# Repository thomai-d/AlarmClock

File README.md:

# AlarmClock
Arduino based alarm clock with wake up light

## Features
* Two individually configurable alarm times
* 15 minutes before alarm, the power-LED is slowly ramped on
* LED wake up color is configurable by the user
* Slowly rising acoustic alarm
* Temperature and air pressure trend for the last 8 hours
* Display brightness is automatically reduced in the dark (LDR)
* Power fail safe (battery buffered RTC)

## Hardware
* atmega328 @ 16MHz
* 2.8" SPI TFT Screen (320x240) with ILI9331 controller
* DS3231 battery buffered RTC with I2C interface
* BMP180 temperature / pressure sensor with I2C interface
* High Power RGB-LED (~4.5W)
* Eagle files / part list included

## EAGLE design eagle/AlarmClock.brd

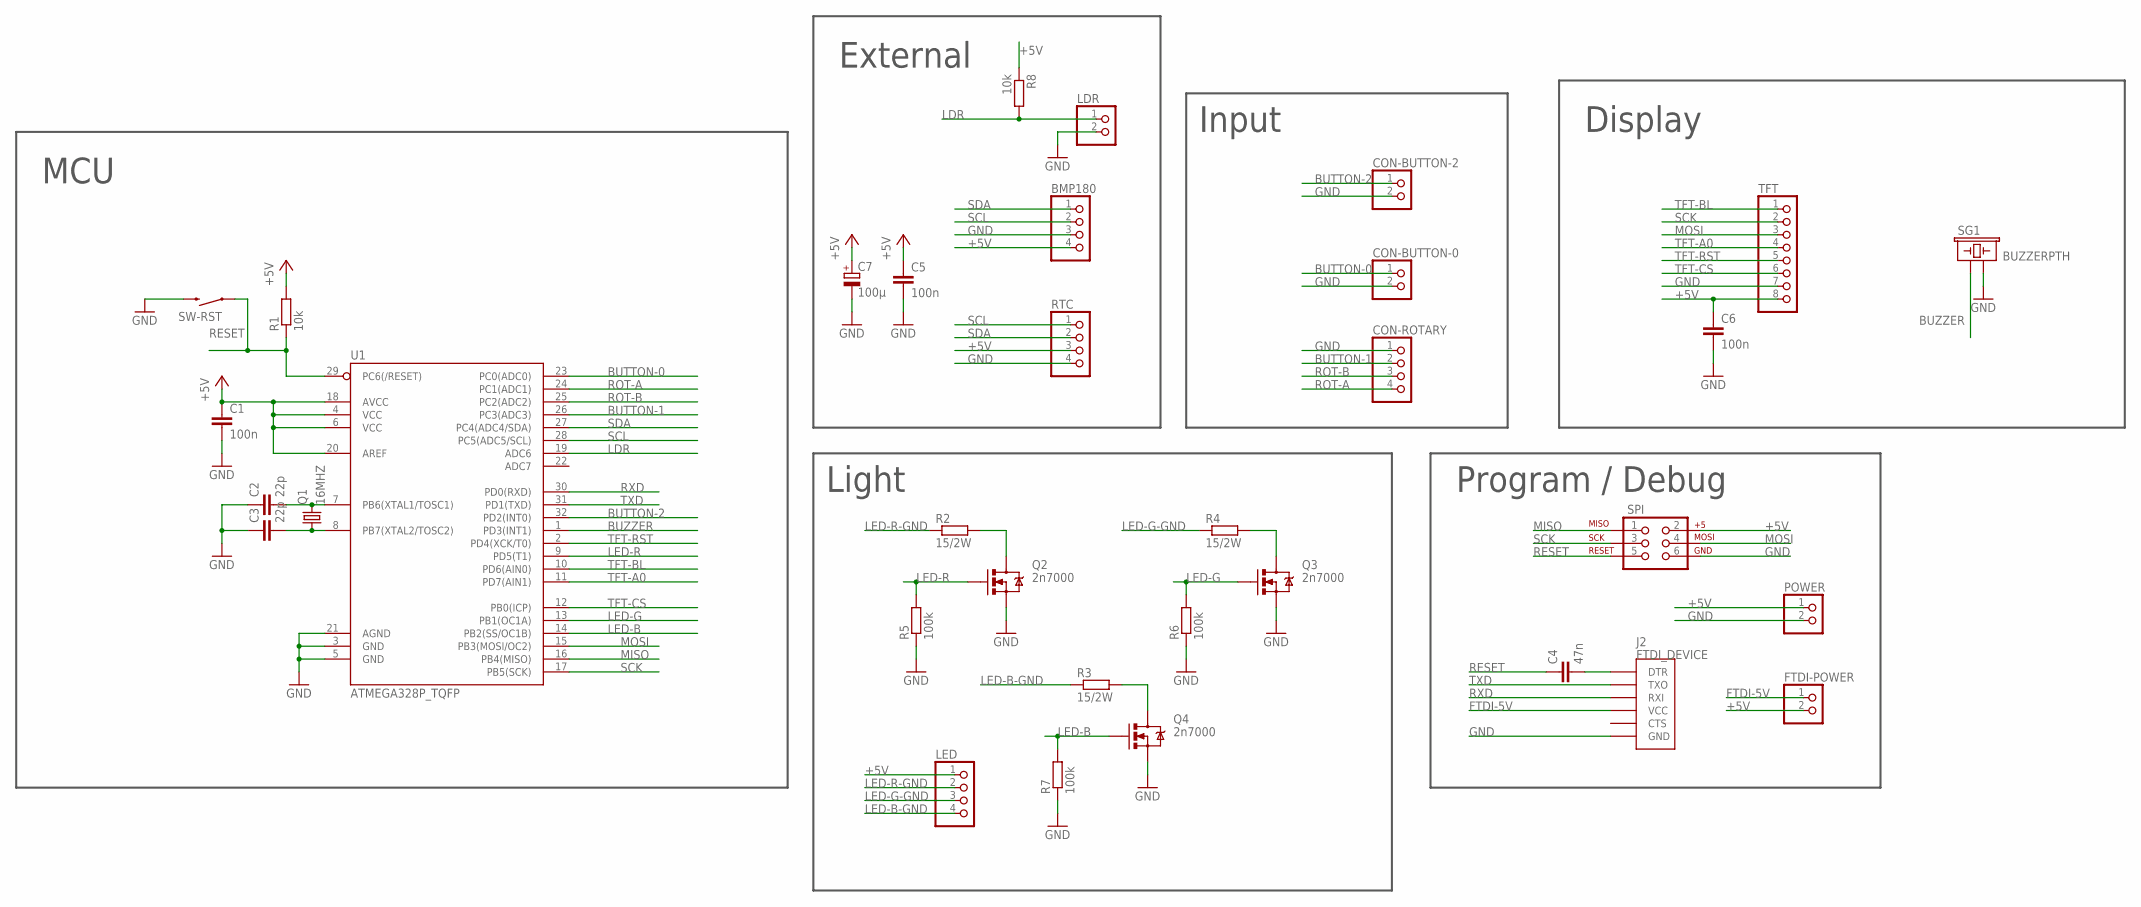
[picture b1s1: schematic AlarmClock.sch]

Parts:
BMP180: 1X04
C1, C5, C6: 100n; C0805
C2, C3: 22p; C0805
C4: 47n; C0805
C7: 100µ; PANASONIC_F
CON-BUTTON-0, CON-BUTTON-2: 1X02/90
CON-ROTARY: 1X04/90
FTDI-POWER: 1X02
J2: FTDI_DEVICE; FTDI_DEVICE_SIDE
LDR: 1X02
LED: 1X04
POWER: 1X02
Q1: 16MHZ; HC49UP
Q2, Q3, Q4: 2n7000; TO-92
R1: 10k; M0805
R2, R3, R4: 15/2W; 0414/15
R5, R6, R7: 100k; M0805
R8: 10k; R0805
RTC: 1X04
SG1: BUZZERPTH; BUZZER-12MM
SPI: AVR_SPI_PRG_6NS; 2X3-NS
SW-RST: SWITCH-MOMENTARY-2SMD-1101NE; TACTILE-SWITCH-1101NE
TFT: 1X08
U1: ATMEGA328P_TQFP; TQFP32-08

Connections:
+5V: BMP180.4, C1.1, C5.1, C6.1, C7.+, FTDI-POWER.2, LED.1, POWER.1, R1.2, R8.1, RTC.3, SPI.2, TFT.8, U1.4 (VCC), U1.6 (VCC), U1.18 (AVCC), U1.20 (AREF)
BUTTON-0: CON-BUTTON-0.1, U1.23 (PC0(ADC0))
BUTTON-1: CON-ROTARY.2, U1.26 (PC3(ADC3))
BUTTON-2: CON-BUTTON-2.1, U1.32 (PD2(INT0))
BUZZER: SG1.+ (1), U1.1 (PD3(INT1))
FTDI-5V: FTDI-POWER.1, J2.P$4 (VCC)
GND: BMP180.3, C1.2, C2.1, C3.1, C5.2, C6.2, C7.-, CON-BUTTON-0.2, CON-BUTTON-2.2, CON-ROTARY.1, J2.P$6 (GND), LDR.2, POWER.2, Q2.1 (S), Q3.1 (S), Q4.1 (S), R5.1, R6.1, R7.1, RTC.4, SG1.- (2), SPI.6, SW-RST.2, TFT.7, U1.3 (GND), U1.5 (GND), U1.21 (AGND)
LDR: LDR.1, R8.2, U1.19 (ADC6)
LED-B: Q4.2 (G), R7.2, U1.14 (PB2(SS/OC1B))
LED-B-GND: LED.4, R3.1
LED-G: Q3.2 (G), R6.2, U1.13 (PB1(OC1A))
LED-G-GND: LED.3, R4.1
LED-R: Q2.2 (G), R5.2, U1.9 (PD5(T1))
LED-R-GND: LED.2, R2.1
MISO: SPI.1, U1.16 (PB4(MISO))
MOSI: SPI.4, TFT.3, U1.15 (PB3(MOSI/OC2))
unnamed: C4.2, J2.P$1 (DTR)
unnamed: C2.2, Q1.2, U1.7 (PB6(XTAL1/TOSC1))
unnamed: C3.2, Q1.1, U1.8 (PB7(XTAL2/TOSC2))
unnamed: Q2.3 (D), R2.2
unnamed: Q3.3 (D), R4.2
unnamed: Q4.3 (D), R3.2
RESET: C4.1, R1.1, SPI.5, SW-RST.1, U1.29 (PC6(/RESET))
ROT-A: CON-ROTARY.4, U1.24 (PC1(ADC1))
ROT-B: CON-ROTARY.3, U1.25 (PC2(ADC2))
RXD: J2.P$3 (RXI), U1.30 (PD0(RXD))
SCK: SPI.3, TFT.2, U1.17 (PB5(SCK))
SCL: BMP180.2, RTC.1, U1.28 (PC5(ADC5/SCL))
SDA: BMP180.1, RTC.2, U1.27 (PC4(ADC4/SDA))
TFT-A0: TFT.4, U1.11 (PD7(AIN1))
TFT-BL: TFT.1, U1.10 (PD6(AIN0))
TFT-CS: TFT.6, U1.12 (PB0(ICP))
TFT-RST: TFT.5, U1.2 (PD4(XCK/T0))
TXD: J2.P$2 (TXO), U1.31 (PD1(TXD))

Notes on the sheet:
External
Input
Light
Program / Debug
Display
MCU

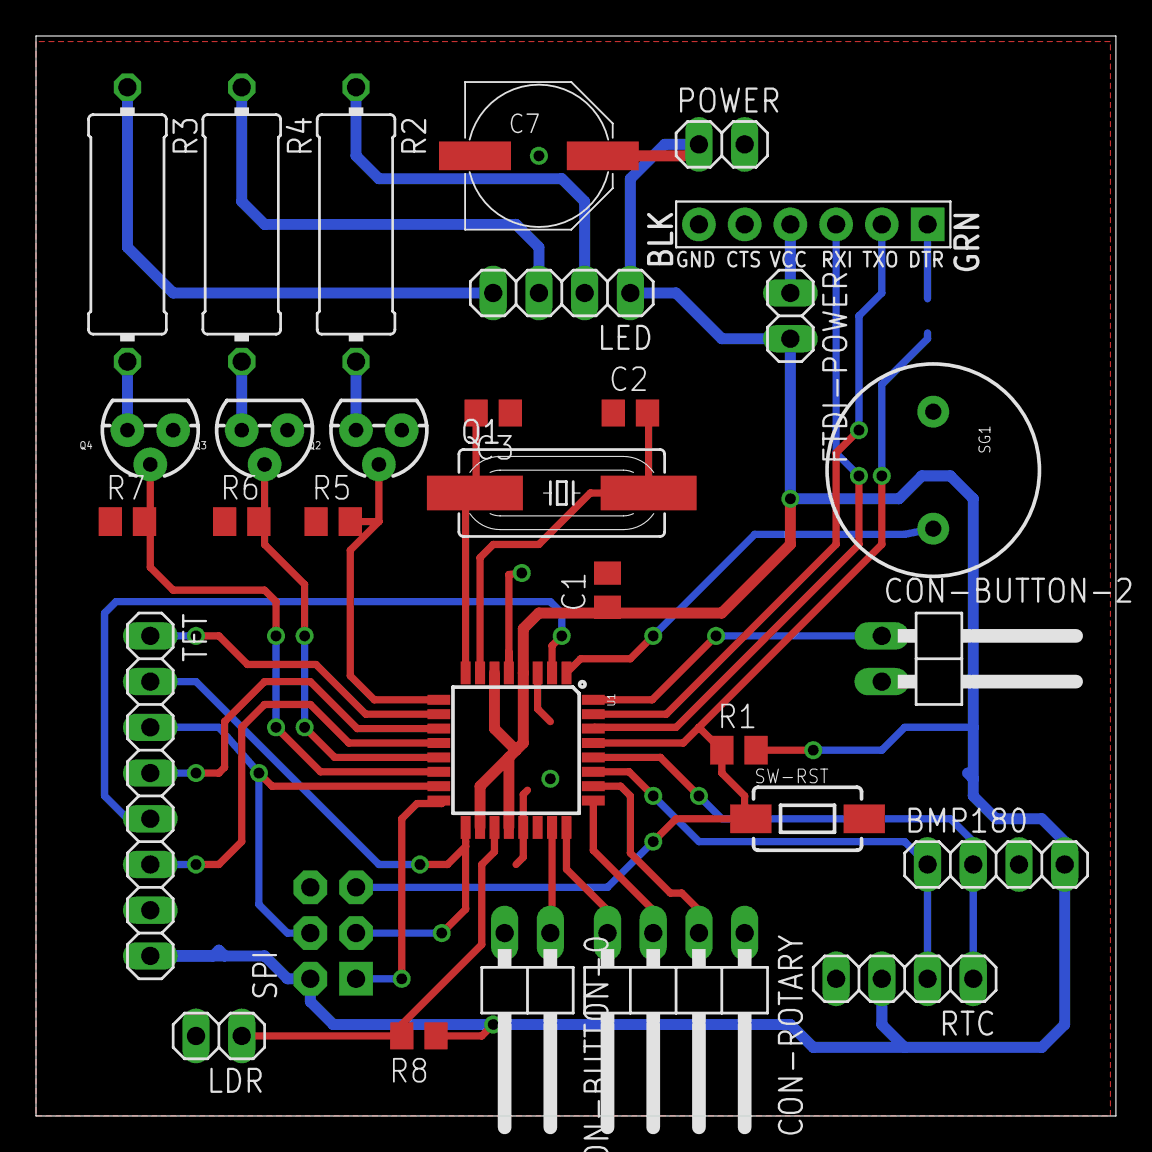
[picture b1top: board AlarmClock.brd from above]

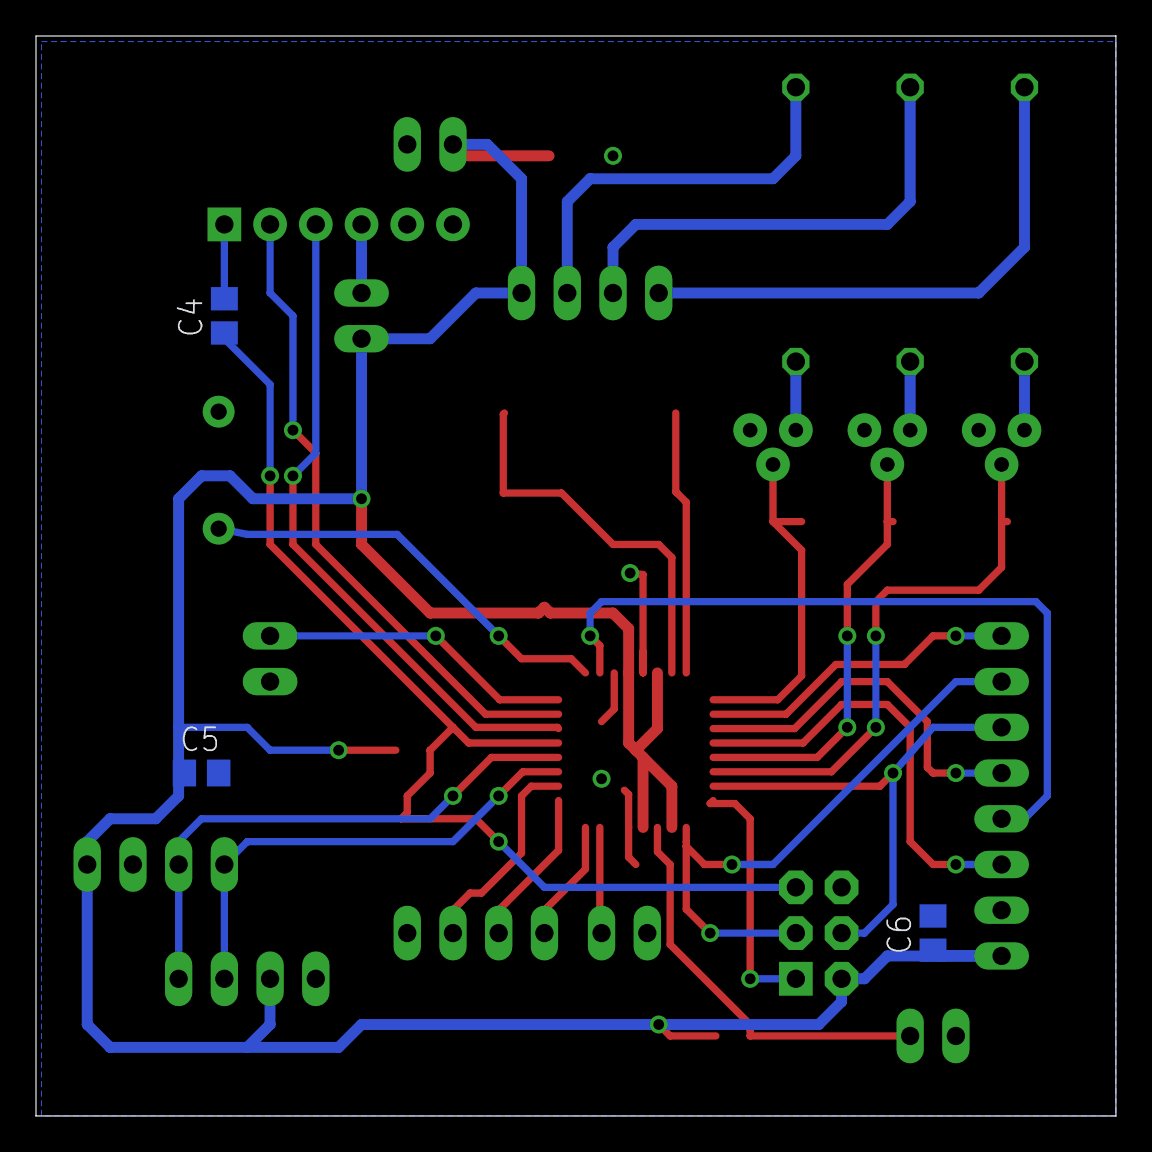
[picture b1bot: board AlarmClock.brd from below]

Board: 2 copper layers, 60.0 x 60.0 mm, 34 parts (3 on the bottom side), 34 nets.

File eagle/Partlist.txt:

Partlist

Exported from AlarmClock.sch at 08.12.2016 19:17

EAGLE Version 7.6.0 Copyright (c) 1988-2016 CadSoft

Assembly variant: 

Part         Value           Device                       Package               Library                    Sheet

BMP180                       PINHD-1X4                    1X04                  pinhead                    1
C1           100n            C-EUC0805                    C0805                 resistor                   1
C2           22p             C-EUC0805                    C0805                 resistor                   1
C3           22p             C-EUC0805                    C0805                 resistor                   1
C4           47n             C-EUC0805                    C0805                 resistor                   1
C5           100n            C-EUC0805                    C0805                 resistor                   1
C6           100n            C-EUC0805                    C0805                 resistor                   1
C7           100µ            CPOL-EUF                     PANASONIC_F           resistor                   1
CON-BUTTON-0                 PINHD-1X2/90                 1X02/90               pinhead                    1
CON-BUTTON-2                 PINHD-1X2/90                 1X02/90               pinhead                    1
CON-ROTARY                   PINHD-1X4/90                 1X04/90               pinhead                    1
FTDI-POWER                   PINHD-1X2                    1X02                  pinhead                    1
J2           FTDI_DEVICE     FTDI_DEVICE                  FTDI_DEVICE_SIDE      SparkFun-Connectors        1
LDR                          PINHD-1X2                    1X02                  pinhead                    1
LED                          PINHD-1X4                    1X04                  pinhead                    1
POWER                        PINHD-1X2                    1X02                  pinhead                    1
Q1           16MHZ           CRYSTALHC49UP                HC49UP                crystal                    1
Q2           2n7000          MOSFET-NCHANNEL2N7000        TO-92                 SparkFun-DiscreteSemi      1
Q3           2n7000          MOSFET-NCHANNEL2N7000        TO-92                 SparkFun-DiscreteSemi      1
Q4           2n7000          MOSFET-NCHANNEL2N7000        TO-92                 SparkFun-DiscreteSemi      1
R1           10k             R-EU_M0805                   M0805                 resistor                   1
R2           15/2W           R-EU_0414/15                 0414/15               resistor                   1
R3           15/2W           R-EU_0414/15                 0414/15               resistor                   1
R4           15/2W           R-EU_0414/15                 0414/15               resistor                   1
R5           100k            R-EU_M0805                   M0805                 resistor                   1
R6           100k            R-EU_M0805                   M0805                 resistor                   1
R7           100k            R-EU_M0805                   M0805                 resistor                   1
R8           10k             R-EU_R0805                   R0805                 resistor                   1
RTC                          PINHD-1X4                    1X04                  pinhead                    1
SG1          BUZZERPTH       BUZZERPTH                    BUZZER-12MM           SparkFun-Electromechanical 1
SPI                          AVR_SPI_PRG_6NS              2X3-NS                SparkFun-Connectors        1
SW-RST                       SWITCH-MOMENTARY-2SMD-1101NE TACTILE-SWITCH-1101NE SparkFun-Electromechanical 1
TFT                          PINHD-1X8                    1X08                  pinhead                    1
U1           ATMEGA328P_TQFP ATMEGA328P_TQFP              TQFP32-08             SparkFun-DigitalIC         1

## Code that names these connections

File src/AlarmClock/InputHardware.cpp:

#include "InputHardware.h"

const uint8_t InputHardwareClass::lookupTable[7][4] = {
	{ R_START,    R_CW_BEGIN,  R_CCW_BEGIN, R_START },
	{ R_CW_NEXT,  R_START,     R_CW_FINAL,  R_START | DIR_CW },
	{ R_CW_NEXT,  R_CW_BEGIN,  R_START,     R_START },
	{ R_CW_NEXT,  R_CW_BEGIN,  R_CW_FINAL,  R_START },
	{ R_CCW_NEXT, R_START,     R_CCW_BEGIN, R_START },
	{ R_CCW_NEXT, R_CCW_FINAL, R_START,     R_START | DIR_CCW },
	{ R_CCW_NEXT, R_CCW_FINAL, R_CCW_BEGIN, R_START }
};

InputHardwareClass::InputHardwareClass()
{
	cli();

	// Setup pins.
	DDRC &= !(_BV(DDC0) | _BV(DDC1) | _BV(DDC2) | _BV(DDC3));
	PORTC |= _BV(PC0) | _BV(PC1) | _BV(PC2) | _BV(PC3);
	pinMode(DI_BUTTON2, INPUT_PULLUP);

	// Setup PCINT.
	PCICR |= _BV(PCIE1);		// Enable PCINT1
	PCIFR |= _BV(PCIF1);		// Clear pending PCINT1
	PCMSK1 |= _BV(PCINT8)		// Enable pins.
		| _BV(PCINT9)
		| _BV(PCINT10)
		| _BV(PCINT11);

	// Setup INT0.
	bitClear(EICRA, ISC00);		// Configure INT0 on
	bitSet(EICRA, ISC01);		// Falling edge.
	bitSet(EIMSK, INT0);		// Enable interrupt.

	sei();
}

void InputHardwareClass::Initialize()
{
	UserActivityManager.ReportUserActivity();
}

void InputHardwareClass::OnINT0()
{
	cli();

	if (this->blockModeButton)
		return;

	uint32_t timeMs = millis();
	uint32_t delta = timeMs - b2_lastEvent;
	if (delta > BUTTON_DEBOUNCE_MS)
	{
		OnButton2Down();

		this->b2_lastEvent = timeMs;
		UserActivityManager.ReportUserActivity();
	}

	sei();
}

uint8_t InputHardwareClass::ReadBrightness()
{
#ifdef NO_LDR
	return 240;
#else
	return analogRead(AI_LDR) >> 2;
#endif
}

void InputHardwareClass::OnPCINT1()
{
	cli();
	
	uint8_t pinc = PINC;

	// Check buttons.
	bool b0wasUp = bitRead(button_states, BUTTON0_BIT);
	bool b1wasUp = bitRead(button_states, BUTTON1_BIT);
	bool b0isUp = bitRead(pinc, BUTTON0_BIT);
	bool b1isUp = bitRead(pinc, BUTTON1_BIT);

	bool b0Changed = b0wasUp != b0isUp;
	bool b1Changed = b1wasUp != b1isUp;
	if (b0Changed || b1Changed)
	{
		uint32_t timeMs = millis();
		UserActivityManager.ReportUserActivity();

		if (b0Changed)
		{
			uint32_t delta = timeMs - b0_lastEvent;
			if (delta > BUTTON_DEBOUNCE_MS)
			{
				if (Focus && !blockInput)
				{
					if (b0isUp)
					{
						Focus->OnButton0Up(delta);
					}
					else
					{
						Focus->OnButton0Down();
					}
				}

				b0_lastEvent = timeMs;
				bitWrite(button_states, BUTTON0_BIT, b0isUp);
			}
		}

		if (b1Changed)
		{
			uint32_t delta = timeMs - b1_lastEvent;
			if (delta > BUTTON_DEBOUNCE_MS)
			{
				if (Focus && (!blockInput || Focus->ForceReceiveButton1()))
				{
					if (b1isUp)
					{
						Focus->OnButton1Up(delta);
					}
					else
					{
						Focus->OnButton1Down();
					}
				}

				b1_lastEvent = timeMs;
				bitWrite(button_states, BUTTON1_BIT, b1isUp);
			}
		}

		sei();
	}

	
	// Check rotary.
	rotary_state = lookupTable[rotary_state & 0xf][(pinc >> 1) & 3];

	if (Focus && !blockInput)
	{
		UserActivityManager.ReportUserActivity();

		switch (rotary_state & 0x30)
		{
		case DIR_CW:
#ifdef ALTERNATIVE_ROTARY
			Focus->OnRotaryChanged(-1);
#else
			Focus->OnRotaryChanged(+1);
#endif
			break;

		case DIR_CCW:
#ifdef ALTERNATIVE_ROTARY
			Focus->OnRotaryChanged(+1);
#else
			Focus->OnRotaryChanged(-1);
#endif
			break;
		}
	}
}

ISR(PCINT1_vect)
{
	cli();
	InputHardware.OnPCINT1();
	sei();
}

ISR(INT0_vect)
{
	cli();
	InputHardware.OnINT0();
	sei();
}

InputHardwareClass InputHardware;

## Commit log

2017-01-29 Added readme
2017-01-29 Fixed image
2017-02-17 Added config for #5
2017-03-23 Improved manual
2020-10-05 Fixed alarm redraw bug
2020-10-05 Implemented night light

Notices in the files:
parts and their libraries:
SparkFun-Connectors: Licensing: Creative Commons ShareAlike 4.0 International - https://creativecommons.org/licenses/by-sa/4.0
